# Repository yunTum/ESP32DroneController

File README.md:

# ESP32DroneController

## Debug Software

## Web Setting

## FlightAnalyzer

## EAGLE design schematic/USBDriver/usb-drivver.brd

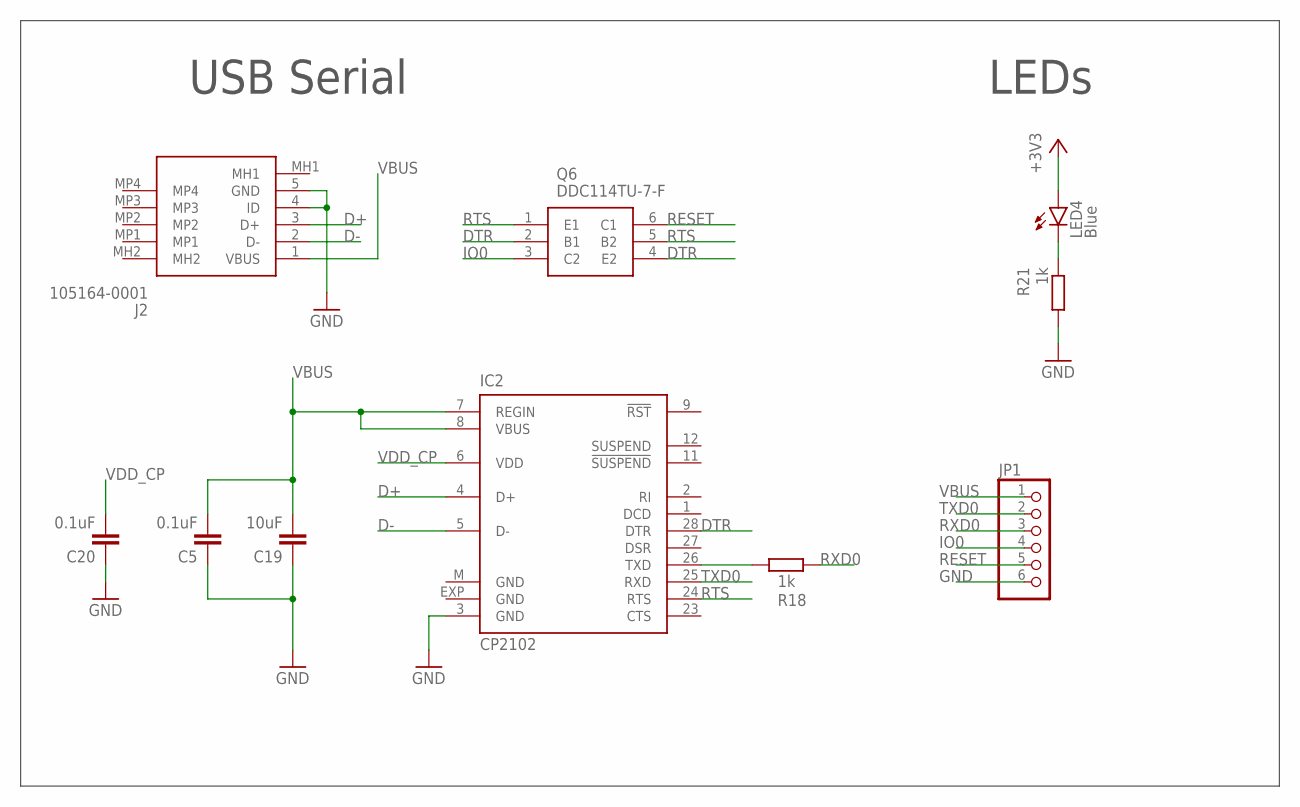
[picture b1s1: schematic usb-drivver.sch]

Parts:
C5, C20: 0.1uF; C0805
C19: 10uF; C0805
IC2: CP2102; MLP28
J2: 105164-0001; 1051640001
JP1: PINHD-1X6; 1X06
LED4: Blue; CHIP-LED0805
Q6: DDC114TU-7-F; SOT65P210X110-6N
R18, R21: 1k; R0805

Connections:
+3V3: LED4.A
D+: IC2.4 (D+), J2.3 (D+)
D-: IC2.5 (D-), J2.2 (D-)
DTR: IC2.28 (DTR), Q6.2 (B1), Q6.4 (E2)
GND: C5.1, C19.1, C20.1, IC2.3 (GND), IC2.EXP (GND), IC2.M (GND), J2.4 (ID), J2.5 (GND), JP1.6, R21.2
IO0: JP1.4, Q6.3 (C2)
unnamed: IC2.26 (TXD), R18.1
unnamed: LED4.C, R21.1
RESET: JP1.5, Q6.6 (C1)
RTS: IC2.24 (RTS), Q6.1 (E1), Q6.5 (B2)
RXD0: JP1.3, R18.2
TXD0: IC2.25 (RXD), JP1.2
VBUS: C5.2, C19.2, IC2.7 (REGIN), IC2.8 (VBUS), J2.1 (VBUS), JP1.1
VDD_CP: C20.2, IC2.6 (VDD)

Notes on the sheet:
USB Serial
LEDs

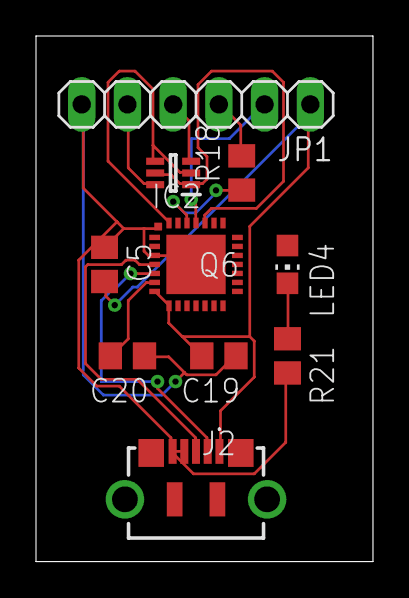
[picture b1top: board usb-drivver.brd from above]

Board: 2 copper layers, 18.7 x 29.2 mm, 10 parts (0 on the bottom side), 13 nets.

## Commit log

2024-10-11 RC値の変更
2024-11-06 add hardware
2024-12-01 fix contoller
    上書きされていたのを修正
2025-01-07 add sch
2025-01-07 add frame
2025-01-28 add LED
2025-01-28 add V2 schematic
2025-01-30 update V2
2025-02-06 add analyzer
2025-02-06 update V1
2025-02-06 update frame
2025-02-10 update pid&esc
2025-02-10 update stable-flight
2025-02-10 update flight-analyzer
2025-02-12 update pid& add alt
2025-02-12 update analyzer
2025-03-14 add filter
2025-03-18 update gui
2025-04-02 update stableV2
2025-04-02 update software
2025-04-02 fix analyzer
